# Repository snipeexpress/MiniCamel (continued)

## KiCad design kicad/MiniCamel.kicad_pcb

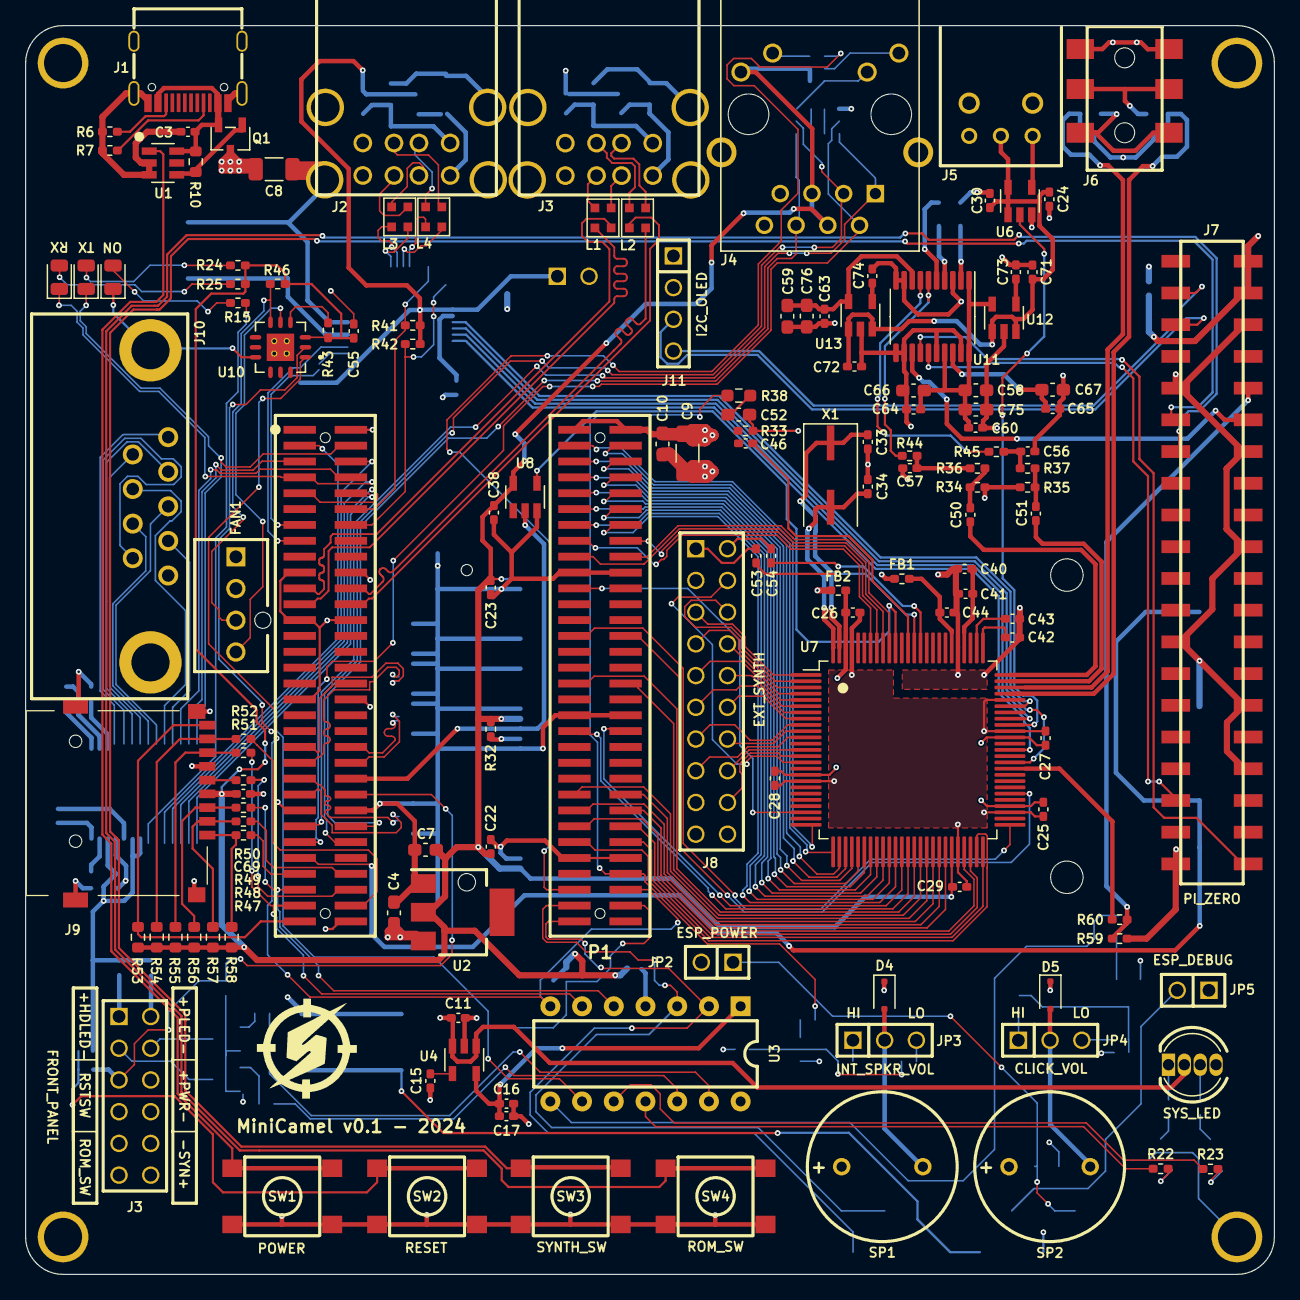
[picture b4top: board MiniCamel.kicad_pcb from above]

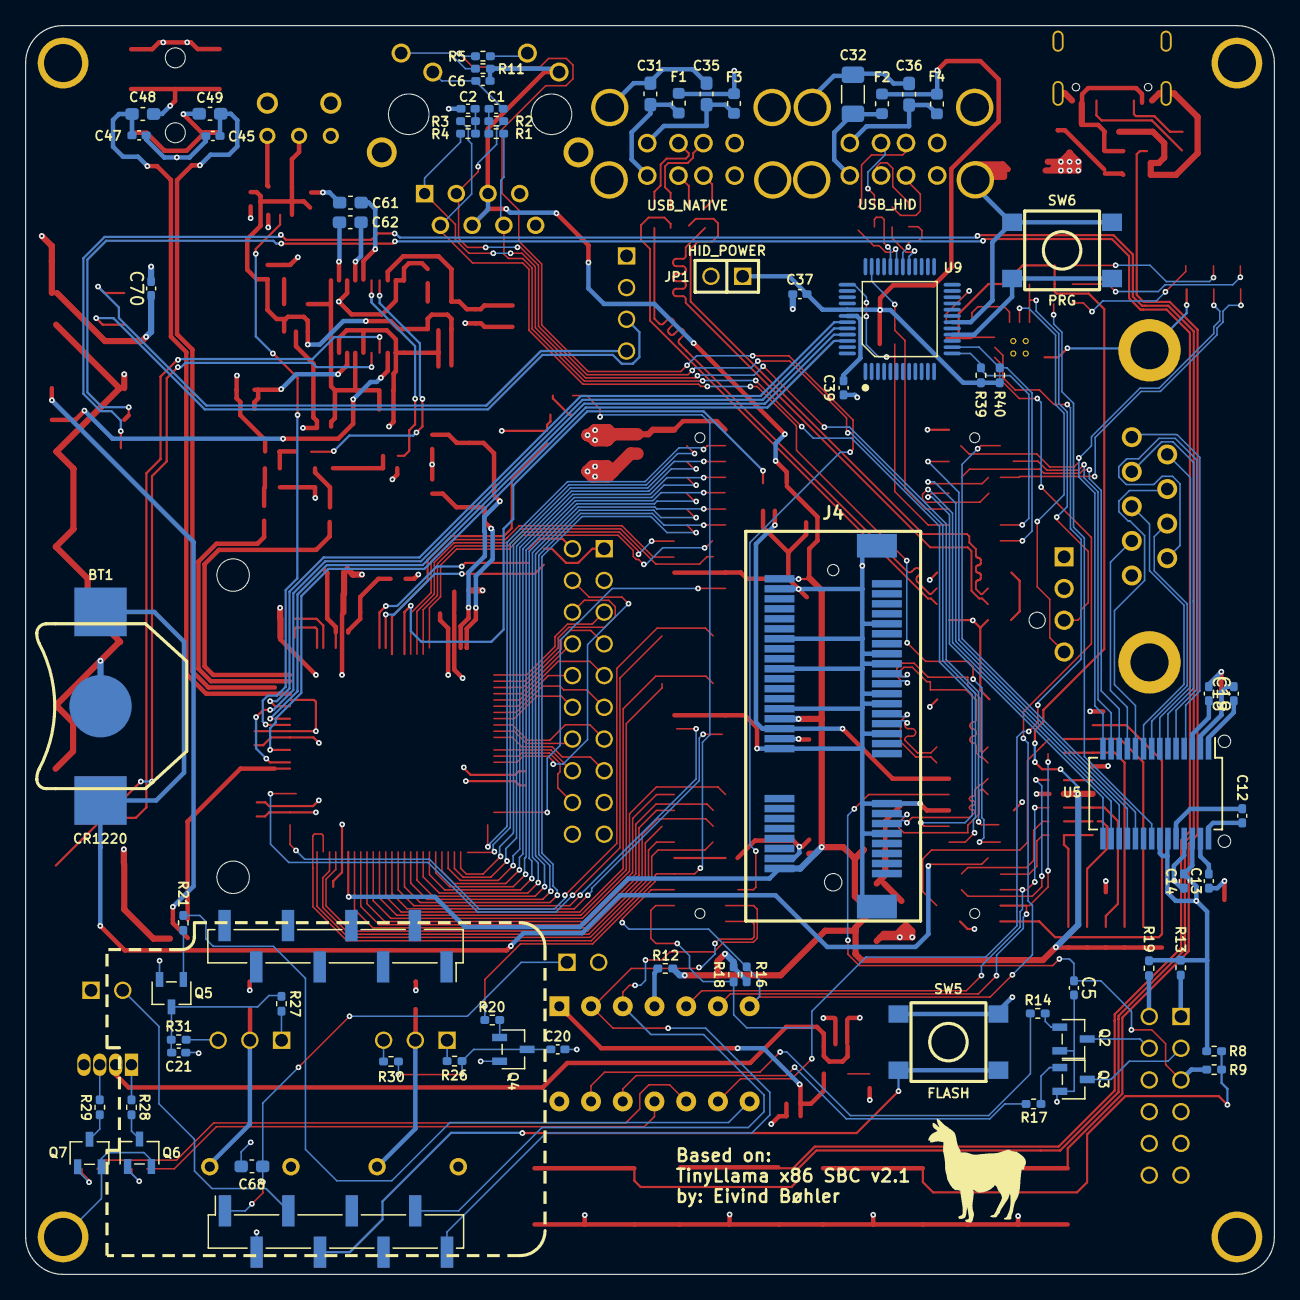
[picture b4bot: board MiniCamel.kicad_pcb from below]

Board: 4 copper layers, 100.0 x 100.0 mm, 209 parts (69 on the bottom side), 229 nets.

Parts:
BT1: CR1220; BT_MY-1220-03
C1, C2, C3, C6, C12, C13, C14, C17, C18, C19, C22, C23, C24, C25, C26, C27, C28, C29, C30, C37, C38, C41, C44, C46, C55, C60, C63, C64, C65, C69, C70: 0.1uF; C_0402_1005Metric_Pad0.74x0.62mm_HandSolder
C4, C48, C49, C58, C59, C66, C67, C75, C76: 10uF; C_0603_1608Metric_Pad1.08x0.95mm_HandSolder
C5, C16, C50, C51: 10uF; C_0402_1005Metric_Pad0.74x0.62mm_HandSolder
C7, C31, C35, C36, C68: 47uF; C_0603_1608Metric_Pad1.08x0.95mm_HandSolder
C8: 47uF; C_1206_3216Metric
C9, C32: 47uF; C_1206_3216Metric_Pad1.33x1.80mm_HandSolder
C10: 0.1uF; C_0603_1608Metric_Pad1.08x0.95mm_HandSolder
C11, C40, C53, C54, C71, C72: 1uF; C_0402_1005Metric_Pad0.74x0.62mm_HandSolder
C15, C73, C74: 470pF; C_0402_1005Metric_Pad0.74x0.62mm_HandSolder
C20, C21: 10nF; C_0402_1005Metric_Pad0.74x0.62mm_HandSolder
C33, C34: 22pF; C_0402_1005Metric_Pad0.74x0.62mm_HandSolder
C39: 3.3uF; C_0402_1005Metric_Pad0.74x0.62mm_HandSolder
C42, C43, C45, C47: 1nF; C_0402_1005Metric_Pad0.74x0.62mm_HandSolder
C52: 2.7nF; C_0603_1608Metric_Pad1.08x0.95mm_HandSolder
C56, C57: 2.2nF; C_0402_1005Metric_Pad0.74x0.62mm_HandSolder
C61, C62: 2.2uF; C_0603_1608Metric_Pad1.08x0.95mm_HandSolder
D1: CONN; D_0805_2012Metric
D2: TX; D_0805_2012Metric
D3: RX; D_0805_2012Metric
D4, D5: 1N4148; D_SOD-323F
D6: SYS_LED; D_LED_D5.0mm-4_RGB
F1, F2, F3, F4: F; Fuse_0603_1608Metric
FB1, FB2: FB; R_0402_1005Metric_Pad0.72x0.64mm_HandSolder
H1, H2, H3, H4: H_HOLE; H_440_HOLE
J1: J_USB_C; J_USB_TYPE-C-31-M-12
J2: USB_HID; J_USB_A_C12049
J3: USB_NATIVE; J_USB_A_C12049
J3#2: FRONT_PANEL; P_CONN_PANEL
J4: Wuerth Elektronik 7499010211A; 7499010211A
J4#2: J_MINI_PCIE
J5: J_TOSLINK_ZGY133T10
J6: AudioJack3; J_AUDIO35_C95463
J7: PI_ZERO; J_CONN_RPI_SMD
J8: EXT_SYNTH; J_CONN_02X10
J9: MICRO_SD; J_MicroSD_TF01A
J10: P_DE9M
J11: I2C_OLED; P_CONN_01X04_SQUARE
J12: J_WEMOS_D1_MINI
JP1: HID_POWER; P_CONN_01X02_SQUARE
JP2: ESP_POWER; P_CONN_01X02_SQUARE
JP3: INT_SPKR_VOL; P_CONN_01X03_SQUARE
JP4: CLICK_VOL; P_CONN_01X03_SQUARE
JP5: ESP_DEBUG; P_CONN_01X02_SQUARE
L1, L2, L3, L4: L_EMI_FILTER; L_EMI_FILTER_MCM2012B900GBE
LOGO1: snipe_logo; snipe_96x96px
LOGO2: Llama_logo; LLAMA_LOGO
P1: P_SOM-128-EX; P_CONN_SOM-128-EX
P3: FAN1; J_MOLEX_47053-1000
Q1: Q_PMOS_GDS; Q_PFET_ENH_SOT-23-3
Q2, Q3, Q4, Q5, Q6, Q7: NPN; Q_BJT_SOT-23-3
R1, R2, R3, R4: 49.9; R_0402_1005Metric_Pad0.72x0.64mm_HandSolder
R5, R11, R20, R21, R24, R25: 1k; R_0402_1005Metric_Pad0.72x0.64mm_HandSolder
R6, R7: 5.1k; R_0402_1005Metric_Pad0.72x0.64mm_HandSolder
R8, R12, R14, R17, R22, R23, R46, R60: 10k; R_0402_1005Metric_Pad0.72x0.64mm_HandSolder
R9, R44, R45: 470; R_0402_1005Metric_Pad0.72x0.64mm_HandSolder
R10, R53, R54, R55, R56, R57, R58: 47k; R_0603_1608Metric
R13, R19: 330; R_0402_1005Metric_Pad0.72x0.64mm_HandSolder
R15: 1.5k; R_0402_1005Metric_Pad0.72x0.64mm_HandSolder
R16, R18, R32, R33, R39, R40, R41, R42, R43: 4.7k; R_0402_1005Metric_Pad0.72x0.64mm_HandSolder
R26, R27: 200; R_0402_1005Metric_Pad0.72x0.64mm_HandSolder
R28: 600; R_0402_1005Metric_Pad0.72x0.64mm_HandSolder
R29: 2k; R_0402_1005Metric_Pad0.72x0.64mm_HandSolder
R30, R31, R47, R48, R49, R51, R52: 33; R_0402_1005Metric_Pad0.72x0.64mm_HandSolder
R34, R35, R36, R37: 6.8k; R_0402_1005Metric_Pad0.72x0.64mm_HandSolder
R38: 47k; R_0603_1608Metric_Pad0.98x0.95mm_HandSolder
R50: 0; R_0402_1005Metric_Pad0.72x0.64mm_HandSolder
R59: 20k; R_0402_1005Metric_Pad0.72x0.64mm_HandSolder
SP1, SP2: SPEAKER; SP
SW1: POWER; SW_B3FS-1010
SW2: RESET; SW_B3FS-1010
SW3: SYNTH_SW; SW_B3FS-1010
SW4: ROM_SW; SW_B3FS-1010
SW5: FLASH; SW_B3FS-1010
SW6: PRG; SW_B3FS-1010
U1: U_MAX16054; U_TSOT-23-6
U2: U_AMS1117-3.3; U_SOT-223-3_NOTAB
U3: U_ATTINY84A; U_DIP-14_W7.62mm
U4, U12, U13: U_MIC5219-3.3YM5; U_SOT-23-5
U5: U_MAX3243; U_SSOP-28_5.3x10.2mm_P0.65mm
U6: U_74LVC1G126; U_SOT-23-5
U7: CS4237B-KQ; U_TQFP-100_14x14mm_P0.5mm_HandSoldering
U8: U_74LVC1G04; U_SOT-23-5
U9: U_CH559L; U_QFP-12x12_14x14_Pitch0.5mm
U10: EMC2303; U_EMC2303
U11: PCM5102A; U_TSSOP-20_4.4x6.5mm_P0.65mm
X1: 16.9344MHz; X_Crystal_SMD_HC49S-MINI

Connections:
+3.3V: C6.1, C7.1, C22.1, C23.1, C29.2, C38.1, C55.1, C69.1, J4.4 (TCT), J4.5 (RCT), J4.12 (D3), J4#2.2 (+3V3AUX), J4#2.24 (+3V3AUX), J4#2.52 (+3V3AUX), J9.4 (VDD), R11.1, R12.2, R16.2, R18.2, R24.1, R25.1, R32.2, R43.2, R46.1, R53.1, R54.1, R55.1, R56.1, R57.1, R58.1, U2.2 (VOUT), U7.45 (VD1), U8.5 (VCC), U10.3 (VDD)
+3.3VSB: C16.1, C17.2, U3.1 (VCC), U4.5 (OUT)
+3.3V_PCM_A: C59.1, C63.1, C76.1, U11.8 (AVDD), U13.5 (OUT)
+3.3V_PCM_D: C58.1, C60.1, C64.1, C66.1, C75.1, U11.1 (CPVDD), U11.17 (XSMT), U11.20 (DVDD), U12.5 (OUT)
+5VA: C44.1, FB1.2, U7.81 (VA)
+5VFILT: C25.2, C26.2, C27.2, C28.2, FB2.2, U7.17 (VDF1), U7.54 (VDF4), U7.65 (VDF2), U7.98 (VDF3)
/3.3V_MIDI_OUT: J7.10 (BCM15/RDX), R59.1, R60.2
/A0: P1.B3 (GP70), U7.25 (SA0)
/A1: P1.B4 (GP71), U7.26 (SA1)
/A2: P1.B5 (GP72), U7.27 (SA2)
/A3: P1.B6 (GP73), U7.28 (SA3)
/A4: P1.B7 (GP74), U7.29 (SA4)
/A5: P1.B8 (GP75), U7.30 (SA5)
/A6: P1.B9 (GP76), U7.31 (SA6)
/A7: P1.B10 (GP77), U7.32 (SA7)
/A8: P1.B11 (GP60), U7.33 (SA8)
/A9: P1.B12 (GP61), U7.34 (SA9)
/A10: P1.B13 (GP62), U7.35 (SA10)
/A11: P1.B14 (GP63), U7.36 (SA11)
/A12: P1.B15 (GP64), U7.94 (SA12)
/A13: P1.B16 (GP65), U7.93 (SA13)
/A14: P1.B17 (GP66), U7.92 (SA14)
/A15: P1.B18 (GP67), U7.91 (SA15)
/AEN: P1.B33 (GP44), U7.39 (AEN)
/CTS1: P1.A10 (GP07), U5.15 (TTL_OUT5)
/D0: P1.B47 (GP20), U7.41 (SD0)
/D1: P1.B48 (GP21), U7.42 (SD1)
/D2: P1.B49 (GP22), U7.43 (SD2)
/D3: P1.B50 (GP23), U7.44 (SD3)
/D4: P1.B51 (GP24), U7.47 (SD4)
/D5: P1.B52 (GP25), U7.48 (SD5)
/D6: P1.B53 (GP26), U7.49 (SD6)
/D7: P1.B54 (GP27), U7.50 (SD7)
/DCD1: P1.A3 (GP00), U5.19 (TTL_OUT1)
/DCD2: J12.11 (D4/GPIO2), JP5.2
/DRQ1: P1.B27 (GP56), U7.51 (DRQB(DRQ1*))
/DSR1: P1.A9 (GP06), U5.16 (TTL_OUT4)
/DTR1: P1.A8 (GP05), U5.12 (TTL_IN3)
/FM_A0: J8.18, U7.14 (SCL/XA0)
/FM_A1: J8.16, U7.13 (XA1)
/FM_D0: J8.12, U7.8 (SDA/XD0)
/FM_D1: J8.11, U7.7 (XD1/SCLK)
/FM_D2: J8.10, U7.6 (XD2/SDIN)
/FM_D3: J8.9, U7.5 (XD3/SDOUT)
/FM_D4: J8.8, U7.4 (XD4/FSYNC)
/FM_D5: J8.7, U7.3 (XD5/MCLK)
/FM_D6: J8.6, U7.2 (XD6/LRCK)
/FM_D7: J8.5, U7.1 (XD7/SDATA)
/FM_SYNTH_L: C53.2, J8.1
/FM_SYNTH_R: C54.2, J8.2
/HDD_LED+: J3#2.1, R13.2
/HDD_LED-: J3#2.2, Q3.3 (C)
/HID_VCC: C37.2, F2.1, F4.1, JP1.1, R39.2, R40.2, R41.2, R42.2, U9.41 (VIN5)
/I2S_BCLK: J7.12 (BCM18/PWM0), U11.13 (BCK)
/I2S_DATA: J7.40 (BCM21/SCLK), U11.14 (DIN)
/I2S_LRCLK: J7.35 (BCM19/MISO), U11.15 (LRCK)
/IOCHRDY: P1.B34 (GP45), U7.40 (IOCHRDY)
/IRQ7: P1.B21 (GP50), U7.23 ((INT7*)IRQB)
/JAB1: U7.70 (JAB1), U9.43 (P1.0)
/JAB2: U7.61 (JAB2), U9.44 (P1.1)
/JACX: U7.68 (JACX), U9.45 (P1.2)
/JACY: U7.63 (JACY), U9.46 (P1.3)
/KBCLK: P1.A12 (GP91), R41.1, U9.35 (P0.5)
/KBDATA: P1.A14 (GP93), R42.1, U9.37 (P0.3)
/LAN_RX+: J4.3 (RD+), P1.A54 (LAN_RX+), R2.2
/LAN_RX-: J4.6 (RD-), P1.A52 (LAN_RX-), R1.2
/LAN_TX+: J4.2 (TD-), P1.A53 (LAN_TX+), R3.2
/LAN_TX-: J4.1 (TD+), P1.A51 (LAN_TX-), R4.2
/LINKACT: P1.B59 (GP12), R5.1
/MIDI_AUDIO_L: C57.2, R36.1, R44.2
/MIDI_AUDIO_R: C56.2, R37.1, R45.2
/MIDI_OUT: R60.1, U7.60 (MIDOUT)
/MSCLK: P1.A13 (GP92), R39.1, U9.13 (P3.7)
/MSDATA: P1.A15 (GP94), R40.1, U9.14 (P4.3)
/PE0_CLK+: J4#2.13 (REFCLK+), P1.A47 (PE0_CLK+)
/PE0_CLK-: J4#2.11 (REFCLK-), P1.A45 (PE0_CLK-)
/PE0_RX+: J4#2.33 (PETp0), P1.A43 (PE0_RX+)
/PE0_RX-: J4#2.31 (PETn0), P1.A41 (PE0_RX-)
/PE0_TX+: J4#2.25 (PERp0), P1.A44 (PE0_TX+)
/PE0_TX-: J4#2.23 (PERn0), P1.A42 (PE0_TX-)
/PI_SCL: J7.5 (BCM3/SCL), J11.3 (SCL)
/PI_SDA: J7.3 (BCM2/SDA), J11.4 (SDA)
/PWM1: P3.4 (PWM), U10.5 (PWM1)
/PWM_CLICK: R21.1, U3.8 (PCINT5/OC1B/PA5)
/PWM_GREEN: R23.1, U3.10 (PCINT3/PA3)
/PWM_HDD: R17.1, U3.12 (PCINT1/PA1)
/PWM_PWR: R14.1, U3.13 (PCINT0/PA0)
/PWM_RED: R22.1, U3.11 (PCINT2/PA2)
/PWR_LED+: J3#2.12, R19.2
/PWR_LED-: J3#2.11, Q2.3 (C)
/PWR_SW: SW1.2 (B), U1.1 (IN)
/RI1: P1.A6 (GP03), U5.18 (TTL_OUT2)
/ROM_SW: J7.13 (BCM27), SW4.2 (B)
/RSTDRV: U7.90 (RESDRV), U8.4
/RST_SW: R8.2, R9.2, SW2.2 (B)
/RS_CTS1: J10.8, U5.8 (RS_IN5)
/RS_DCD1: J10.1, U5.4 (RS_IN1)
/RS_DSR1: J10.6, U5.7 (RS_IN4)
/RS_DTR1: J10.4, U5.11 (RS_OUT3)
/RS_RI1: J10.9, U5.5 (RS_IN2)
/RS_RTS1: J10.7, U5.10 (RS_OUT2)
/RS_RX1: J10.2, U5.6 (RS_IN3)
/RS_TX1: J10.3, U5.9 (RS_OUT1)
/RTS1: P1.A5 (GP02), U5.13 (TTL_IN2)
/RX1: D3.1 (K), P1.A7 (GP04), U5.17 (TTL_OUT3)
/RX2: J12.16 (TX/GPIO1), P1.B63 (GP16), U3.2 (PB0/PCINT8)
/SD_CD: J9.9 (CD), P1.A63 (GP86), R53.2
/SD_CLK: P1.A60 (GP83), R50.2
/SD_CMD: P1.A59 (GP82), R49.2, U3.5 (PB2/PCINT10/INT0/OC0A)
/SD_DAT0: P1.A61 (GP84), R51.2, U3.6 (PA7/PCINT7/OC0B)
/SD_DAT1: P1.A62 (GP85), R52.2
/SD_DAT2: P1.A57 (GP80), R47.2
/SD_DAT3: P1.A58 (GP81), R48.2
/SPDIF_OUT: U6.2, U7.67 (JBCX*/SDOUT)
/SPKR: P1.B58 (GP11), R20.1, R38.1
/SYNTH_SW: J7.11 (BCM17), SW3.2 (B)
/TACH1: P3.3 (TACH), R46.2, U10.6 (TACH1)
/TX1: D2.1 (K), P1.A4 (GP01), U5.14 (TTL_IN1)
/TX2: J12.15 (RX/GPIO3), P1.B61 (GP14), U3.3 (PB1/PCINT9)
/USBD1+: L1.3, P1.A23 (USBD1+)
/USBD1-: L1.2, P1.A21 (USBD1-)
/USBD2+: L2.3, P1.A24 (USBD2+)
/USBD2-: L2.2, P1.A22 (USBD2-)
/USBDX1+: J3.3 (D1+), L1.4
/USBDX1-: J3.2 (D1-), L1.1
/USBDX2+: J3.7 (D2+), L2.4
/USBDX2-: J3.6 (D2-), L2.1
/USBHID1+: L3.4, U9.29 (P5.5/HP)
/USBHID1-: L3.1, U9.30 (P5.4/HM)
/USBHID2+: L4.4, U9.31 (P5.1/DP)
/USBHID2-: L4.1, U9.32 (P5.0/DM)
/USBHIDX1+: J2.3 (D1+), L3.3
/USBHIDX1-: J2.2 (D1-), L3.2
/USBHIDX2+: J2.7 (D2+), L4.3
/USBHIDX2-: J2.6 (D2-), L4.2
/V86_SCL: P1.B62 (GP15), R18.1, U3.9 (PCINT4/SCL/PA4), U10.2 (SMCLK)
/V86_SDA: P1.B60 (GP13), R16.1, U3.7 (PA6/PCINT6/OCA1A/SDA), U10.1 (SMDATA)
/VBATT: BT1.1 (+), P1.A55 (VBATT)
/VBUS: C3.2, J1.A4/B9 (VBUS), J1.A9/B4 (VBUS), Q1.3 (S), R10.2, U1.6 (VCC)
/X_SD_CLK: J9.5 (CLK), R50.1
/X_SD_CMD: J9.3 (CMD), R49.1, R56.2
/X_SD_DAT0: J9.7 (DAT0), R51.1, R55.2
/X_SD_DAT1: J9.8 (DAT1), R52.1, R54.2
/X_SD_DAT2: J9.1 (DAT2), R47.1, R58.2
/X_SD_DAT3: J9.2 (DAT3/CD), R48.1, R57.2
/~BRESET: J8.4, U7.15 (~BRESET)
/~DACK1: P1.B28 (GP57), U7.56 (~DACKB(~DACK1*))
/~FM_CS: J8.13, U7.9 (~SCS/~UP)
/~FM_RD: J8.14, U7.10 (~XIOR)
/~FM_WR: J8.15, U7.11 (~XIOW)
/~IOR: P1.B40 (GP31), U7.37 (~IOR)
/~IOW: P1.B39 (GP30), U7.38 (~IOW)
/~PCIRST: J4#2.22 (~PERST), P1.A46 (~PCIRST), U8.2
/~RST_SW: C5.1, J3#2.3, P1.A48 (~RESET), R9.1
GND: BT1.2 (-), C1.2, C2.2, C3.1, C4.2, C5.2, C6.2, C7.2, C8.2, C9.2, C10.2, C11.2, C13.2, C14.2, C15.2, C16.2, C17.1, C19.1, C20.2, C21.2, C22.2, C23.2, C24.1, C25.1, C26.1, C27.1, C28.1, C29.1, C30.2, C31.2, C32.2, C33.1, C34.1, C35.2, C36.2, C37.1, C38.2, C39.1, C40.2, C41.2, C42.2, C43.2, C44.2, C45.2, C47.2, C52.2, C55.2, C56.1, C57.1, C58.2, C59.2, C60.2, C61.1, C63.2, C64.2, C65.1, C66.2, C67.1, C68.2, C69.2, C70.2, C71.2, C72.2, C73.2, C74.2, C75.2, C76.2, D1.1 (K), H1.1, H2.1, H3.1, H4.1, J1.A1/B12 (GND), J1.A12/B1 (GND), J1.S (SHIELD), J2.4 (GND1), J2.8 (GND2), J2.S (Shield), J3.4 (GND1), J3.8 (GND2), J3.S (Shield), J3#2.4, J3#2.5, J3#2.8, J3#2.9, J4.8 (C1), J4.10 (D2), J4.CASE@1, J4.CASE@2, J4#2.4 (GND), J4#2.9 (GND), J4#2.15 (GND), J4#2.18 (GND), J4#2.21 (GND), J4#2.26 (GND), J4#2.27 (GND), J4#2.29 (GND), J4#2.34 (GND), J4#2.35 (GND), J4#2.37 (GND), J4#2.40 (GND), J4#2.43 (GND), J4#2.50 (GND), J4#2.S1 (SHIELD), J4#2.S2 (SHIELD), J5.3 (GND), J6.S, J7.6 (GND), J7.9 (GND), J7.14 (GND), J7.20 (GND), J7.25 (GND), J7.30 (GND), J7.34 (GND), J7.39 (GND), J8.3, J8.20, J9.6 (VSS), J9.S (Shield), J10.5, J10.10 (GND), J10.11 (GND), J11.1 (GND), J12.10 (GND), JP5.1, P1.A2 (GND), P1.A19 (GND), P1.A20 (GND), P1.A25 (AGND), P1.A26 (AGND), P1.A35 (GND), P1.A36 (GND), P1.A49 (GND), P1.A50 (GND), P1.A64 (GP87), P1.B19 (GND), P1.B20 (GND), P1.B37 (GND), P1.B38 (GND), P1.B55 (GND), P1.B56 (GND), P3.1 (GND), Q2.2 (E), Q3.2 (E), Q4.2 (E), Q5.2 (E), Q6.2 (E), Q7.2 (E), R6.2, R7.2, R33.2, R34.2, R35.2, R59.2, SW1.1 (A), SW2.1 (A), SW3.1 (A), SW4.1 (A), SW5.2 (B), SW6.2 (B), U1.2 (GND), U1.3 (CLEAR), U2.1 (GND), U3.14 (GND), U4.2 (GND), U5.25 (GND), U6.3 (GND), U7.18 (SGND1), U7.46 (DGND1), U7.53 (SGND4), U7.66 (SGND2), U7.71 (TEST), U7.80 (AGND), U7.97 (SGND3), U8.3 (GND), U9.18 (GND), U10.9 (CLK), U10.13 (GND), U11.3 (CPGND), U11.9 (AGND), U11.10 (DEMP), U11.11 (FLT), U11.12 (SCK), U11.16 (FMT), U11.19 (DGND), U12.2 (GND), U13.2 (GND)
unnamed: C1.1, R1.1, R2.1
unnamed: C2.1, R3.1, R4.1
unnamed: C46.2, C52.1, R33.1, R38.2
unnamed: C48.2, J6.R
unnamed: C49.2, J6.T
unnamed: C50.2, R34.1, R36.2
unnamed: C51.2, R35.1, R37.2
unnamed: D1.2 (A), R15.2
unnamed: D2.2 (A), R24.2
unnamed: D3.2 (A), R25.2
unnamed: D4.2 (A), JP3.2, SP1.2
unnamed: D5.2 (A), JP4.2, SP2.2
unnamed: D6.3 (GK), R29.2
unnamed: D6.1 (RK), R28.2
unnamed: J1.A5 (CC1), R7.1
unnamed: J1.B5 (CC2), R6.1
unnamed: J4.9 (D1), R11.2
unnamed: J4.11 (D4), R5.2
unnamed: J4#2.20 (~W_DISABLE), R32.1
unnamed: JP3.1, R26.2
unnamed: JP3.3, R30.2
unnamed: JP4.1, R27.2
unnamed: JP4.3, R31.2
unnamed: C31.1, F1.2, J3.1 (VBUS1)
unnamed: C35.1, F3.2, J3.5 (VBUS2)
unnamed: C32.1, F2.2, J2.1 (VBUS1)
unnamed: C36.1, F4.2, J2.5 (VBUS2)
unnamed: J5.1 (VIN), U6.4
unnamed: C68.1, J12.9 (5V), JP2.1
unnamed: J12.12 (D3/GPIO0), SW5.1 (A)
unnamed: Q1.1 (G), R10.1, U1.4 (~OUT)
unnamed: Q2.1 (B), R14.2
unnamed: Q3.1 (B), R17.2
unnamed: Q4.1 (B), R20.2
unnamed: C20.1, Q4.3 (C), R26.1, R30.1
unnamed: Q5.1 (B), R21.2
unnamed: C21.1, Q5.3 (C), R27.1, R31.1
unnamed: Q6.1 (B), R22.2
unnamed: Q6.3 (C), R28.1
unnamed: Q7.1 (B), R23.2
unnamed: Q7.3 (C), R29.1
unnamed: SW6.1 (A), U9.16 (P4.6)
unnamed: R12.1, U3.4 (PB3/PCINT11/~RESET)
unnamed: C15.1, U4.4 (BYP)
unnamed: C12.1, U5.28 (C1+)
unnamed: C12.2, U5.24 (C1-)
unnamed: C18.1, U5.1 (C2+)
unnamed: C18.2, U5.2 (C2-)
unnamed: C13.1, U5.27 (V+)
unnamed: C19.2, U5.3 (V-)
unnamed: R15.1, U5.21 (~INVALID)
unnamed: C50.1, U7.75 (LAUX1)
unnamed: C43.1, U7.77 (LFILT)
unnamed: C53.1, U7.87 (LLINE)
unnamed: C45.1, C49.1, U7.73 (LOUT)
unnamed: C46.1, U7.88 (MIN)
unnamed: C51.1, U7.74 (RAUX1)
unnamed: C40.1, C41.1, U7.79 (REFFLT)
unnamed: C42.1, U7.76 (RFILT)
unnamed: C54.1, U7.86 (RLINE)
unnamed: C47.1, C48.1, U7.72 (ROUT)
unnamed: C34.2, U7.100 (XTALI), X1.2
unnamed: C33.2, U7.99 (XTALO), X1.1
unnamed: C39.2, U9.42 (VDD33)
unnamed: R43.1, U10.4 (ADDR_SEL)
unnamed: C62.2, U11.4 (CAPM)
unnamed: C62.1, U11.2 (CAPP)
unnamed: C65.2, C67.2, U11.18 (LDOO)
unnamed: R44.1, U11.6 (OUTL)
unnamed: R45.1, U11.7 (OUTR)
unnamed: C61.2, U11.5 (VNEG)
unnamed: C73.1, U12.4 (BYP)
unnamed: C74.1, U13.4 (BYP)
VCC: C4.1, C8.1, C9.1, C10.1, C11.1, C14.1, C24.2, C30.1, C70.1, C71.1, C72.1, D4.1 (K), D5.1 (K), D6.2 (A), F1.1, F3.1, FB1.1, FB2.1, J5.2 (VCC), J7.2 (5v), J7.4 (5v), J8.17, J11.2 (VCC), JP1.2, JP2.2, P1.B1 (VCC), P1.B2 (VCC), P3.2 (VDD), Q1.2 (D), R8.1, R13.1, R19.1, SP1.1, SP2.1, U2.3 (VIN), U4.1 (IN), U4.3 (EN), U5.22 (~FORCEOFF), U5.23 (FORCEON), U5.26 (VCC), U6.1 (OE), U6.5 (VCC), U12.1 (IN), U12.3 (EN), U13.1 (IN), U13.3 (EN)

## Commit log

2024-06-26 Delete case directory
    will need to create a new case since the board dimensions are different
2024-06-26 Delete kicad directory
    will upload
2024-06-26 Delete INITBIOS.IMG
    will upload custom
2024-06-26 Create kicad
2024-06-26 Create test
2025-06-02 250602_initial
2025-06-02 250602_01
    forgot to retain the readme.md
2025-06-05 250605-01
    updated revision numbers on schematic
